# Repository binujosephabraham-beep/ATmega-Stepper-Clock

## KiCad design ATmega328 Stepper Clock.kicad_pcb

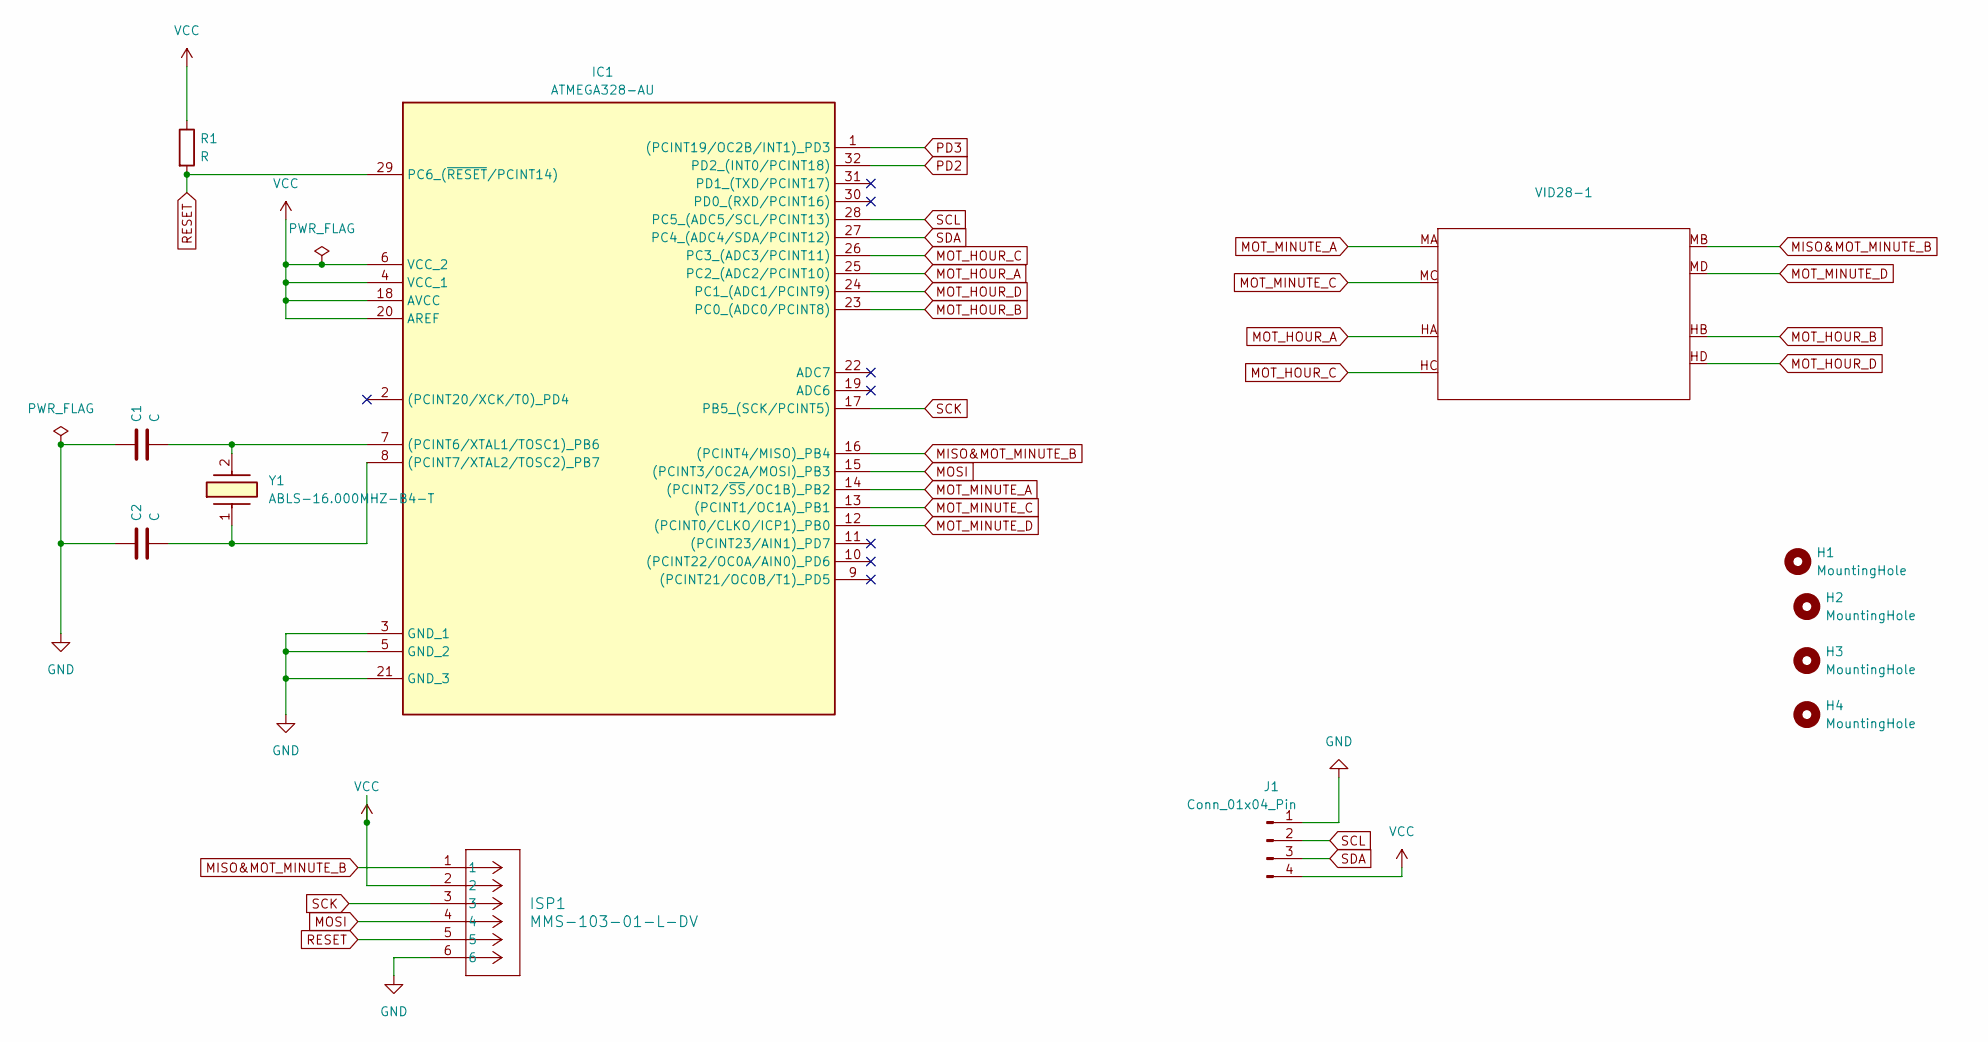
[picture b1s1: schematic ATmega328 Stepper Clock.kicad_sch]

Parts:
C1, C2: C; C_0805_2012Metric
H1, H2, H3, H4: MountingHole; MountingHole_3mm
IC1: ATMEGA328-AU; QFP80P900X900X120-32N; Manufacturer_Part_Number ATMEGA328-AU; Mouser Part Number 556-ATMEGA328-AU
ISP1: MMS-103-01-L-DV; CON6_2X3_UH_MMS_SAI
J1: Conn_01x04_Pin; Wago_734-134_1x04_P3.50mm_Vertical
R1: R; R_1206_3216Metric
VID28-1: VID28-05
Y1: ABLS-16.000MHZ-B4-T; ABLS; Manufacturer_Part_Number ABLS-16.000MHZ-B4-T; Mouser Part Number 815-ABLS-16.0M-T

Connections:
GND: C1.1, C2.1, IC1.3 (GND_1), IC1.5 (GND_2), IC1.21 (GND_3), ISP1.6, J1.1
MISO&MOT_MINUTE_B: IC1.16 ((PCINT4/MISO)_PB4), ISP1.1, VID28-1.MB
MOSI: IC1.15 ((PCINT3/OC2A/MOSI)_PB3), ISP1.4
MOT_HOUR_A: IC1.25 (PC2_(ADC2/PCINT10)), VID28-1.HA
MOT_HOUR_B: IC1.23 (PC0_(ADC0/PCINT8)), VID28-1.HB
MOT_HOUR_C: IC1.26 (PC3_(ADC3/PCINT11)), VID28-1.HC
MOT_HOUR_D: IC1.24 (PC1_(ADC1/PCINT9)), VID28-1.HD
MOT_MINUTE_A: IC1.14 ((PCINT2/~SS/OC1B)_PB2), VID28-1.MA
MOT_MINUTE_C: IC1.13 ((PCINT1/OC1A)_PB1), VID28-1.MC
MOT_MINUTE_D: IC1.12 ((PCINT0/CLKO/ICP1)_PB0), VID28-1.MD
unnamed: C1.2, IC1.7 ((PCINT6/XTAL1/TOSC1)_PB6), Y1.2
unnamed: C2.2, IC1.8 ((PCINT7/XTAL2/TOSC2)_PB7), Y1.1
PD2: IC1.32 (PD2_(INT0/PCINT18))
PD3: IC1.1 ((PCINT19/OC2B/INT1)_PD3)
RESET: IC1.29 (PC6_(~RESET/PCINT14)), ISP1.5, R1.2
SCK: IC1.17 (PB5_(SCK/PCINT5)), ISP1.3
SCL: IC1.28 (PC5_(ADC5/SCL/PCINT13)), J1.2
SDA: IC1.27 (PC4_(ADC4/SDA/PCINT12)), J1.3
VCC: IC1.4 (VCC_1), IC1.6 (VCC_2), IC1.18 (AVCC), IC1.20 (AREF), ISP1.2, J1.4, R1.1

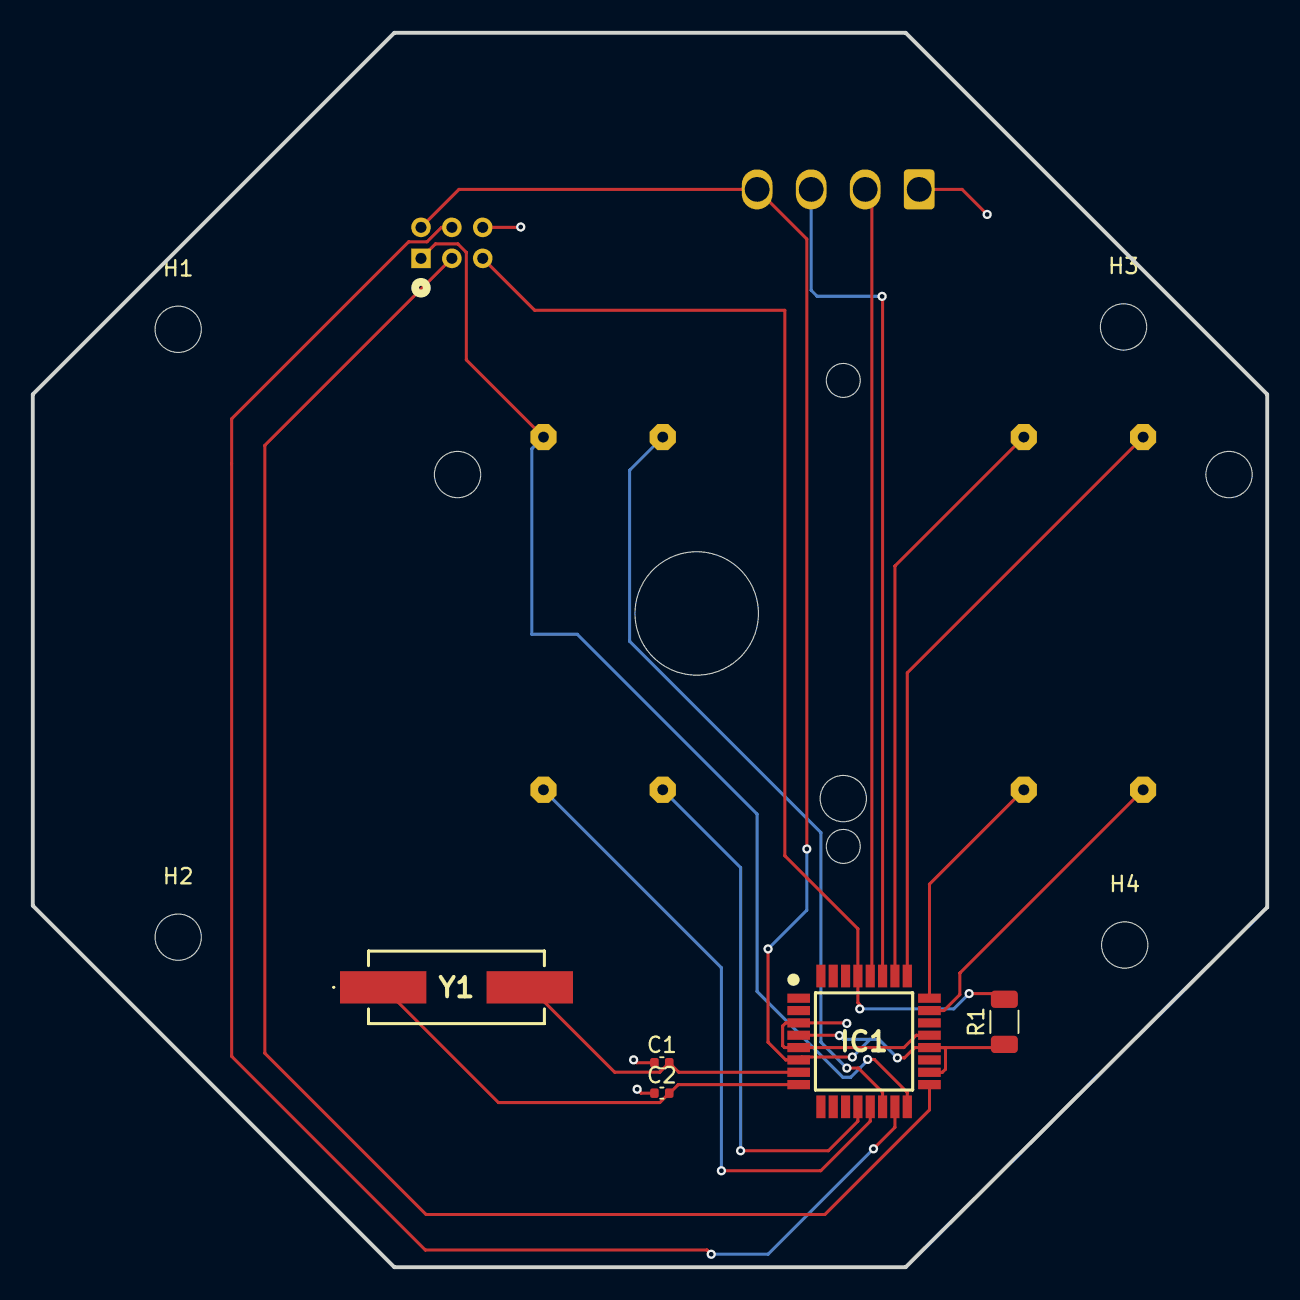
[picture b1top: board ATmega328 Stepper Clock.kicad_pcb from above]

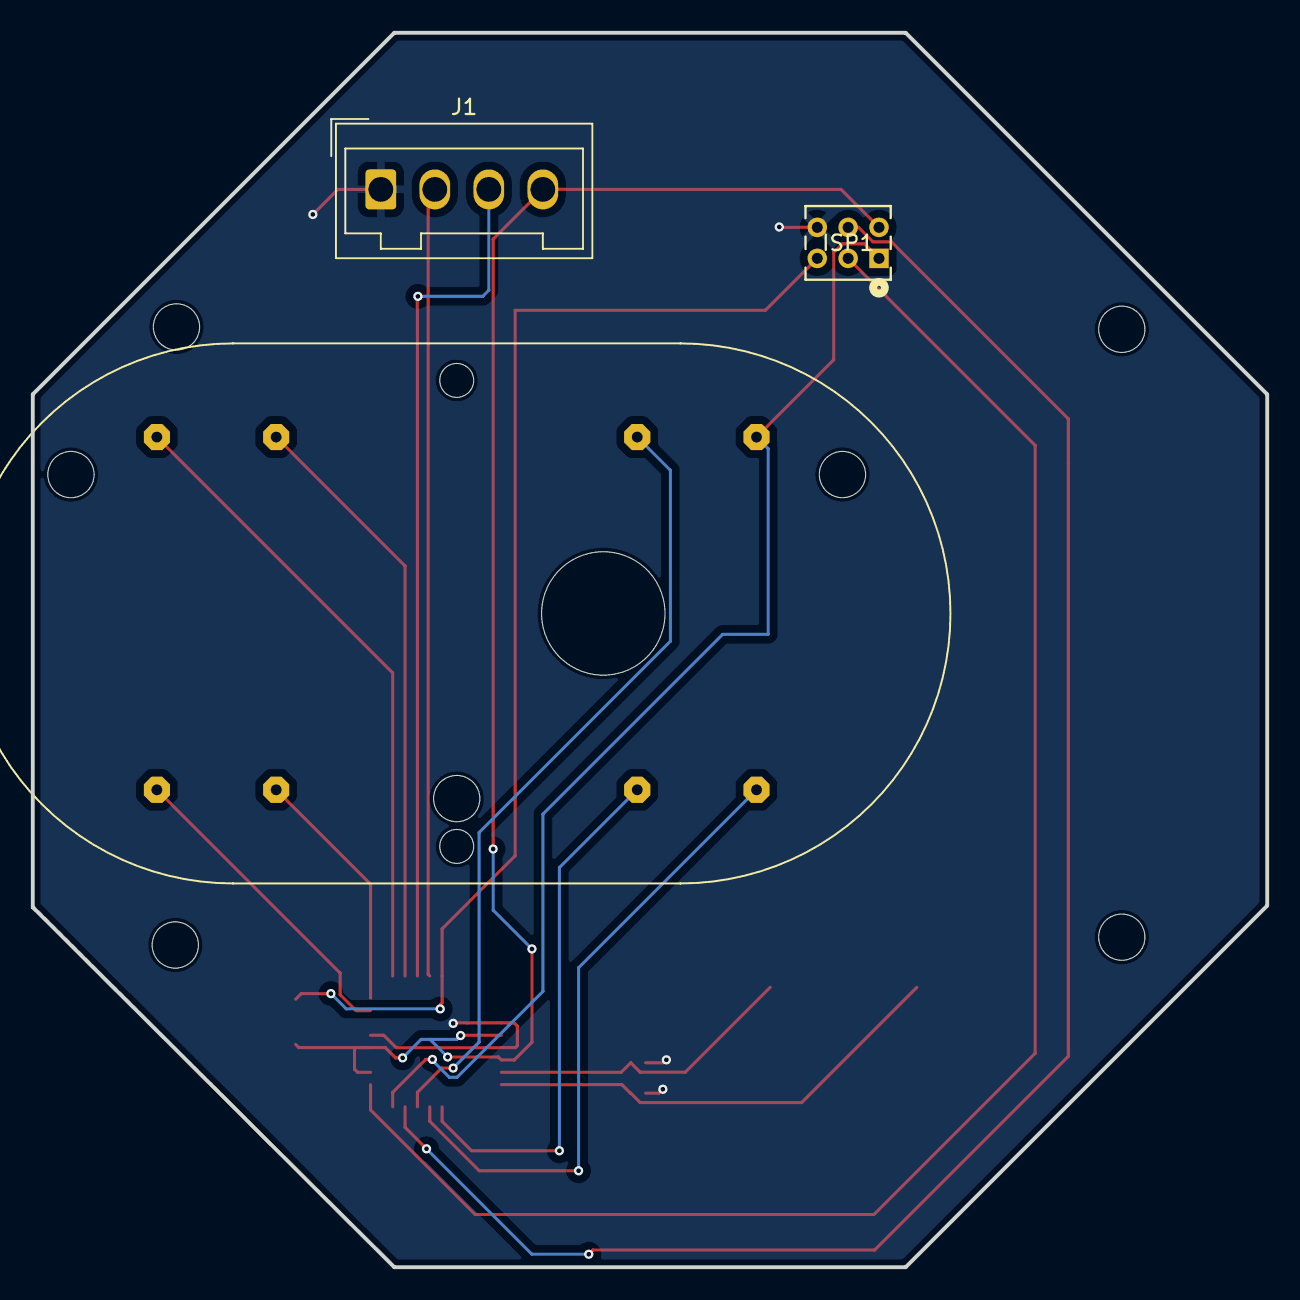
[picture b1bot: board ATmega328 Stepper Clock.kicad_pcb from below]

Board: 2 copper layers, 80.0 x 80.0 mm, 12 parts (3 on the bottom side), 17 nets.

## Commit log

2025-11-11 Temporary symbols and footprints selected ,the dual shaft stepper motor symbol and footprint are nowhere to be found
2025-11-11 changed ATmega328P-AU to ATmega328-au
2025-11-13 Rogh schematic connections done
2025-11-13 Made some changes and assigned footprint for all except stepper motors
2025-11-18 I have made custom symbol for VID28-05 and assigned the footprint for it which sir gave me
2025-11-19 started working on the PCB layout
2025-11-20 Made a rough pcb layout , i made the frame using LibreCAD
2025-12-04 Had to lot of changes like delete 10pin connectors,replace the DIN with 4-pin connector , hole size 3mm im starting the pcb layout all over again
2025-12-05 changed the crystal to one which was available in the mouser website again made the PCB layout , all the SMD components are on the front and the THT are in the bottom
